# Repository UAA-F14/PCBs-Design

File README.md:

# Power Electronics PCBs

Power electronics boards from coursework — physical PCB designs, not just simulation. Each folder is a separate board with its own schematic/layout, a 3D render, and (coming soon) real photos of the built board.

| | Project | What it is |
|---|---|---|
|  | [`scr-controller/`](scr-controller/) | SCR/thyristor phase-control firing board |
|  | [`buck-converter-24-120v/`](buck-converter-24-120v/) | Buck converter, 24 V input target |
|  | [`classd-amplifier-stm32/`](classd-amplifier-stm32/) | Class D amplifier, STM32-controlled switching |
|  | [`power-supply-protected/`](power-supply-protected/) | Voltage supply with short-circuit protection (power + control boards) |
|  | [`ac-dc-inverter/`](ac-dc-inverter/) | AC-DC inverter |

All of these were built as coursework together with [Iker Garcia](https://github.com/IKGB105) [DasReyxr](https://github.com/DasReyxr) and [Kevin Lara](https://github.com/Gyonyu) — the original combined project history lives in [DasReyxr/HW-Projects](https://github.com/DasReyxr/HW-Projects). This repo pulls out just the PCB projects, one per folder, with proper writeups and renders instead of a mixed dump of exam/simulation files.

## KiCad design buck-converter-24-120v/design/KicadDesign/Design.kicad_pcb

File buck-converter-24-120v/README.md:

# Buck Converter (24 V &rarr; 120 V design exam)

A buck converter built for a power electronics exam. 

## Directory structure
```
├── design
│   ├── SCRController
│   │   ├── Design.kicad_pcb
│   │   ├── Design.kicad_pro
│   │   ├── Design.kicad_sch
│   └── Schematic.pdf
├── README.md
├── src
│   └── render.png
├── sim
    └── BuckConv.ms14
    └── simulation.asc
```

- `BuckConverter.kicad_sch` / `.kicad_pcb` / `.kicad_pro` — KiCad design
- `Schematic.pdf` — schematic printout
- `simulation.asc` — LTspice simulation

**Photos of the built board — coming soon**

## Credit
Built as coursework with [DasReyxr](https://github.com/DasReyxr)  and [Kevin Lara](https://github.com/Gyonyu) — original project history in [DasReyxr/HW-Projects](https://github.com/DasReyxr/HW-Projects). This copy is curated separately with a proper writeup and renders.

## Template
```
mkdir code design doc scripts sim src
```

```
tree >> Readme.md
```

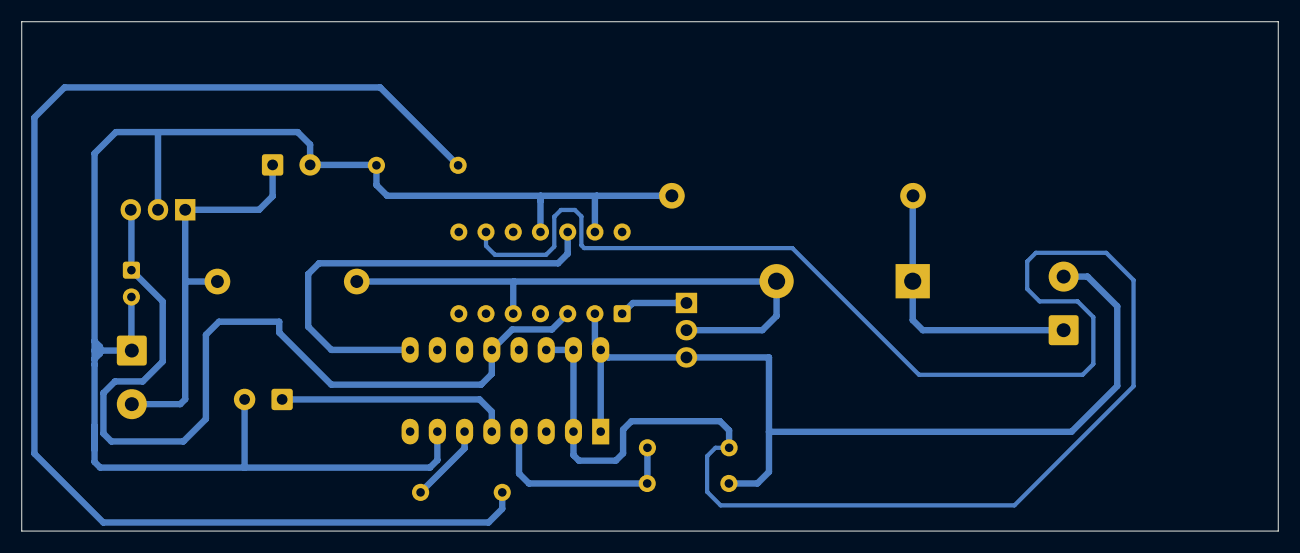
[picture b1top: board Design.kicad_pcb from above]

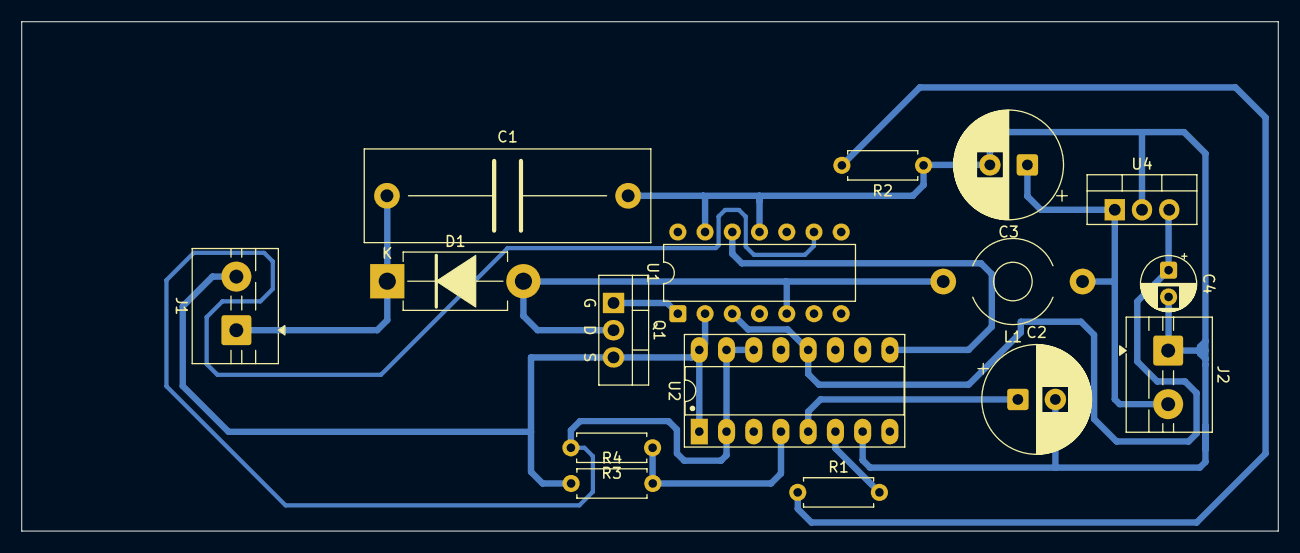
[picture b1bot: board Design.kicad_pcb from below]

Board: 2 copper layers, 117.2 x 47.5 mm, 16 parts (16 on the bottom side), 12 nets.

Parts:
C1: C_Rect_L26.5mm_W8.5mm_P22.50mm; C_Rect_L26.5mm_W8.5mm_P22.50mm_MKS4
C2: 1nF; CP_Radial_D10.0mm_P3.50mm
C3: 470n; CP_Radial_D10.0mm_P3.50mm
C4: 0.1u; CP_Radial_D5.0mm_P2.50mm
D1: MUR460; D_DO-201AD_P12.70mm_Horizontal
J1, J2: Screw_Terminal_01x02; TerminalBlock_MaiXu_MX126-5.0-02P_1x02_P5.00mm
L1: L; L_Toroid_Horizontal_D7.8mm_P13.00mm_Diameter9-5mm_Amidon-T30
Q1: IRF740; TO-220-3_Vertical_GDS
R1, R2, R3, R4: R_0201; R_Axial_DIN0207_L6.3mm_D2.5mm_P7.62mm_Horizontal
U1: IR2110; DIP-14_W7.62mm
U2: TL494; DIP-16_W7.62mm_Socket_LongPads
U4: LM7809CT; TO-220-3_Vertical

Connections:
9V: C4.1, U1.3 (VCC), U2.12 (VCC), U4.3 (OUT)
24V: C3.1, J2.2, L1.1, U4.1 (IN)
D: D1.2 (A), L1.2, Q1.2 (D), U1.5 (VS)
GND: C1.2, C2.2, C3.2, C4.2, J1.2, J2.1, Q1.3 (S), R2.1, R4.1, U1.2 (COM), U1.11 (SD), U1.13 (VSS), U2.1 (1IN+), U2.7 (GND), U2.16 (2IN+), U4.2
unnamed: C1.1, D1.1 (K), J1.1
unnamed: Q1.1 (G), U1.1 (LO)
unnamed: R1.1, R2.2
unnamed: C2.1, U2.5 (CT)
unnamed: R3.1, R4.2, U2.4 (DTC)
unnamed: R1.2, U2.6 (RT)
PWMOUT: U1.12 (LIN), U2.9 (E1)
REF: R3.2, U1.9 (VDD), U2.2 (1IN-), U2.14 (REF), U2.15 (2IN-)

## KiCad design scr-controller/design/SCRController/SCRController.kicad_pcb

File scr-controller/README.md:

# SCR (Thyristor) Firing Controller

A didactic board for triggering SCRs/thyristors — a phase-control firing circuit built for a power electronics course.

## Directory structure
```
├── design
│   ├── KicadDesign
│   │   ├── Design.kicad_pcb
│   │   ├── Design.kicad_pro
│   │   ├── Design.kicad_sch
│   └── Schematic.pdf
├── doc
│   ├── AC
│   ├── ConfigAC.tex
│   ├── Examen1.pdf
│   ├── Examen1.tex
│   └── Tarjeta didáctica de control para tiristores.pdf
├── README.md
├── src
│   └── render.png
├── sim
│   └── SCR.asc
```

- `SCRController.kicad_sch` / `.kicad_pcb` / `.kicad_pro` — KiCad design
- `SCRController.step` — 3D model
- `Tarjeta didáctica de control para tiristores.pdf` — design writeup
- `simulation.asc.txt` — LTspice simulation

**Photos of the built board — coming soon**

## Files

## Credit
Built as coursework with [DasReyxr](https://github.com/DasReyxr)  and [Kevin Lara](https://github.com/Gyonyu) — original project history in [DasReyxr/HW-Projects](https://github.com/DasReyxr/HW-Projects). This copy is curated separately with a proper writeup and renders.

## Template
```
mkdir code design doc scripts sim src
```

```
tree >> README.md
```

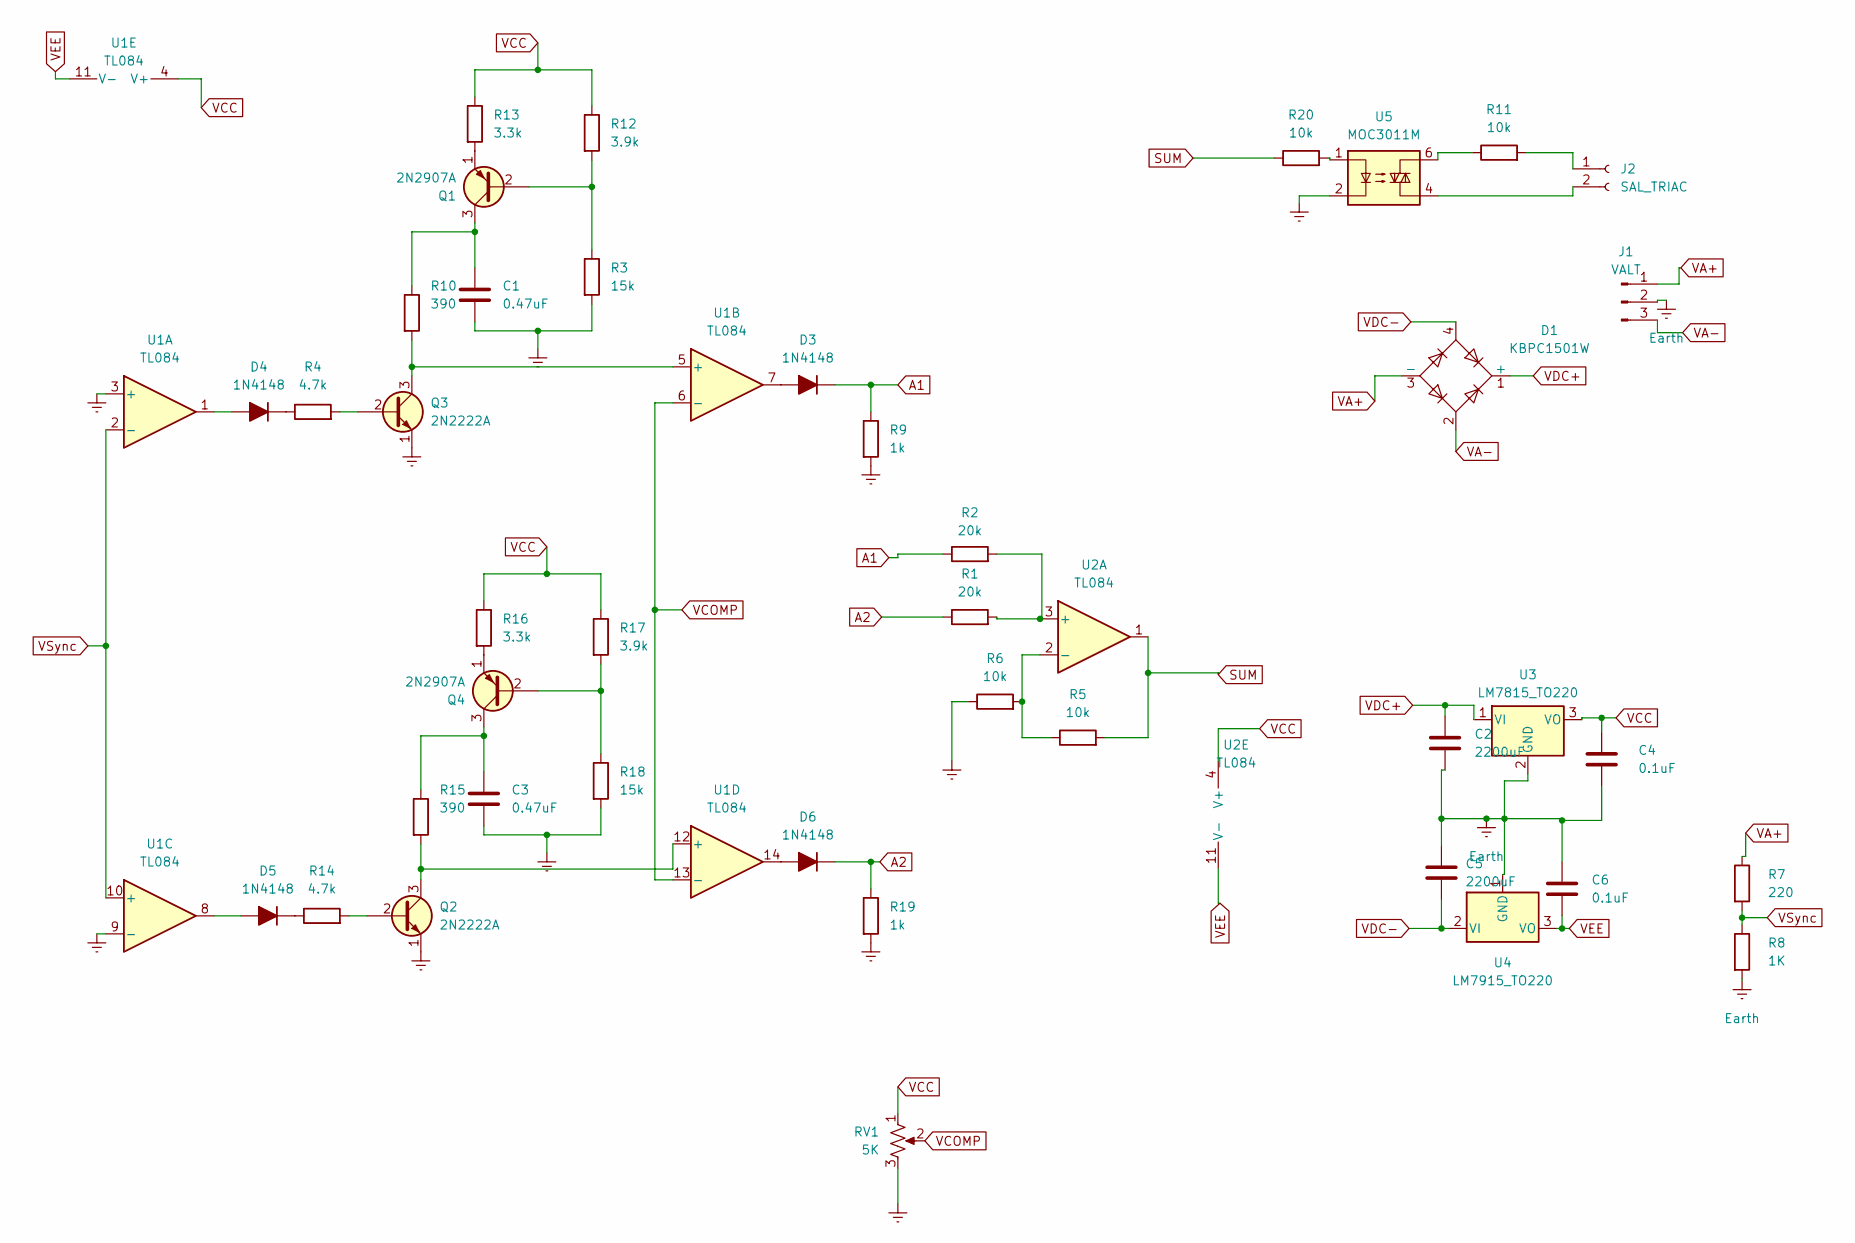
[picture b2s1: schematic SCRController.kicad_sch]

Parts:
C1, C3: 0.47uF; C_Radial_D4.0mm_H5.0mm_P1.50mm
C2, C5: 2200uF; C_Radial_D12.5mm_H25.0mm_P5.00mm
C4, C6: 0.1uF; C_Radial_D4.0mm_H5.0mm_P1.50mm
D1: KBPC1501W; Diode_Bridge_KBP
D3, D4, D5, D6: 1N4148; D_DO-15_P5.08mm_Vertical_AnodeUp
J1: VALT; TerminalBlock_MaiXu_MX126-5.0-03P_1x03_P5.00mm
J2: SAL_TRIAC; TerminalBlock_MaiXu_MX126-5.0-02P_1x02_P5.00mm
Q1, Q4: 2N2907A; TO-92L_Inline_Wide
Q2, Q3: 2N2222A; TO-92L_Inline_Wide
R1, R2: 20k; R_Axial_DIN0207_L6.3mm_D2.5mm_P7.62mm_Horizontal
R3, R18: 15k; R_Axial_DIN0207_L6.3mm_D2.5mm_P7.62mm_Horizontal
R4, R14: 4.7k; R_Axial_DIN0207_L6.3mm_D2.5mm_P7.62mm_Horizontal
R5, R6, R11, R20: 10k; R_Axial_DIN0207_L6.3mm_D2.5mm_P7.62mm_Horizontal
R7: 220; R_Axial_DIN0207_L6.3mm_D2.5mm_P7.62mm_Horizontal
R8: 1K; R_Axial_DIN0207_L6.3mm_D2.5mm_P7.62mm_Horizontal
R9, R19: 1k; R_Axial_DIN0207_L6.3mm_D2.5mm_P7.62mm_Horizontal
R10, R15: 390; R_Axial_DIN0207_L6.3mm_D2.5mm_P7.62mm_Horizontal
R12, R17: 3.9k; R_Axial_DIN0207_L6.3mm_D2.5mm_P7.62mm_Horizontal
R13, R16: 3.3k; R_Axial_DIN0207_L6.3mm_D2.5mm_P7.62mm_Horizontal
RV1: 5K; Potentiometer_Alps_RK163_Single_Horizontal
U1, U2: TL084; DIP-14_W7.62mm_LongPads
U3: LM7815_TO220; TO-220-3_Vertical
U4: LM7915_TO220; TO-220-3_Vertical
U5: MOC3011M; DIP-6_W7.62mm_LongPads

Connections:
A1: D3.1 (K), R2.1, R9.1
A2: D6.1 (K), R1.1, R19.1
Earth: C1.2, C2.2, C3.2, C4.2, C5.1, C6.1, J1.2, Q2.1 (E), Q3.1 (E), R3.2, R6.1, R8.2, R9.2, R18.2, R19.2, RV1.3, U1.3 (+), U1.9 (-), U3.2 (GND), U4.1 (GND), U5.2
unnamed: D3.2 (A), U1.7
unnamed: D4.2 (A), U1.1
unnamed: D4.1 (K), R4.1
unnamed: D5.2 (A), U1.8
unnamed: D5.1 (K), R14.1
unnamed: D6.2 (A), U1.14
unnamed: J2.1, R11.2
unnamed: J2.2, U5.4
unnamed: Q1.2 (B), R3.1, R12.2
unnamed: C1.1, Q1.3 (C), R10.1
unnamed: Q1.1 (E), R13.2
unnamed: Q2.2 (B), R14.2
unnamed: Q2.3 (C), R15.2, U1.12 (+)
unnamed: Q3.2 (B), R4.2
unnamed: Q3.3 (C), R10.2, U1.5 (+)
unnamed: Q4.2 (B), R17.2, R18.1
unnamed: C3.1, Q4.3 (C), R15.1
unnamed: Q4.1 (E), R16.2
unnamed: R11.1, U5.6
unnamed: R20.2, U5.1
unnamed: R1.2, R2.2, U2.3 (+)
unnamed: R5.1, R6.2, U2.2 (-)
SUM: R5.2, R20.1, U2.1
VA+: D1.3 (-), J1.1, R7.1
VA-: D1.2, J1.3
VCC: C4.1, R12.1, R13.1, R16.1, R17.1, RV1.1, U1.4 (V+), U2.4 (V+), U3.3 (VO)
VCOMP: RV1.2, U1.6 (-), U1.13 (-)
VDC+: C2.1, D1.1 (+), U3.1 (VI)
VDC-: C5.2, D1.4, U4.2 (VI)
VEE: C6.2, U1.11 (V-), U2.11 (V-), U4.3 (VO)
VSync: R7.2, R8.1, U1.2 (-), U1.10 (+)

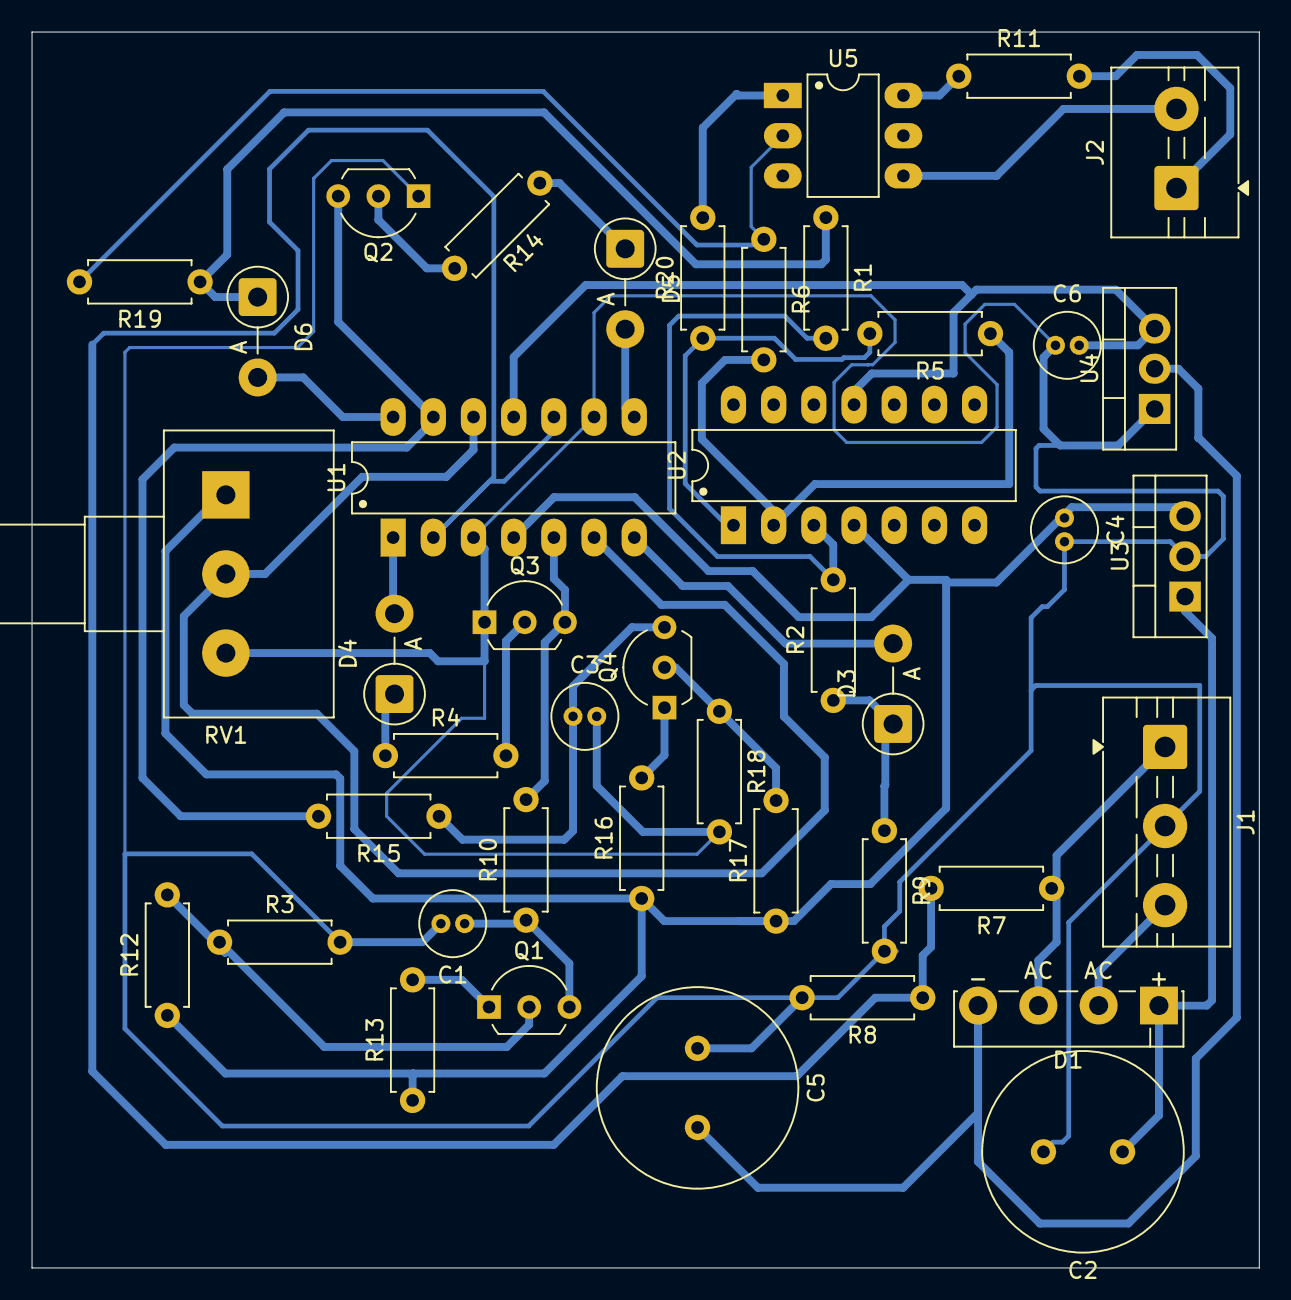
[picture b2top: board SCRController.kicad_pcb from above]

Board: 2 copper layers, 77.6 x 78.1 mm, 43 parts (0 on the bottom side), 34 nets.

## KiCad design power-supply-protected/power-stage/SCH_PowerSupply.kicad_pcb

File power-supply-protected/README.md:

# Protected Voltage Supply (Two-Board System)

A voltage supply with short-circuit protection, split across two boards: a **power stage** (the actual supply, fully routed with fabrication-ready Gerbers) and a **control stage** (protection/sensing logic built around a CD4043BE tri-state buffer).

## Directory structure
```
├── design
│   ├── SCH_PowerSupply
│   └── SCH_PowerSupply.pdf
├── doc
│   ├── generalconfig.tex
│   ├── PowerSupply.pdf
│   ├── PowerSupply.tex
│   ├── sn-jnl.cls
├── Power_Supply.pdf
├── README.md
├── sim
│   └── PowerSupply.ms14
└── src
    └── render.png
```

- `power-stage/` — `SCH_PowerSupply.kicad_*`, full Gerbers + drill files in `gerbers/`, PDF writeup
- `control-stage/` — `CONTROL_PowerSupply.kicad_*`, CD4043BE symbol
- `Power_Supply.pdf` — overall design writeup
- 

**Photos of the built boards — coming soon**

## Credit
Built as coursework with [DasReyxr](https://github.com/DasReyxr) and [Kevin Lara](https://github.com/Gyonyu) — original project history in [DasReyxr/HW-Projects](https://github.com/DasReyxr/HW-Projects). This copy is curated separately with a proper writeup and renders.

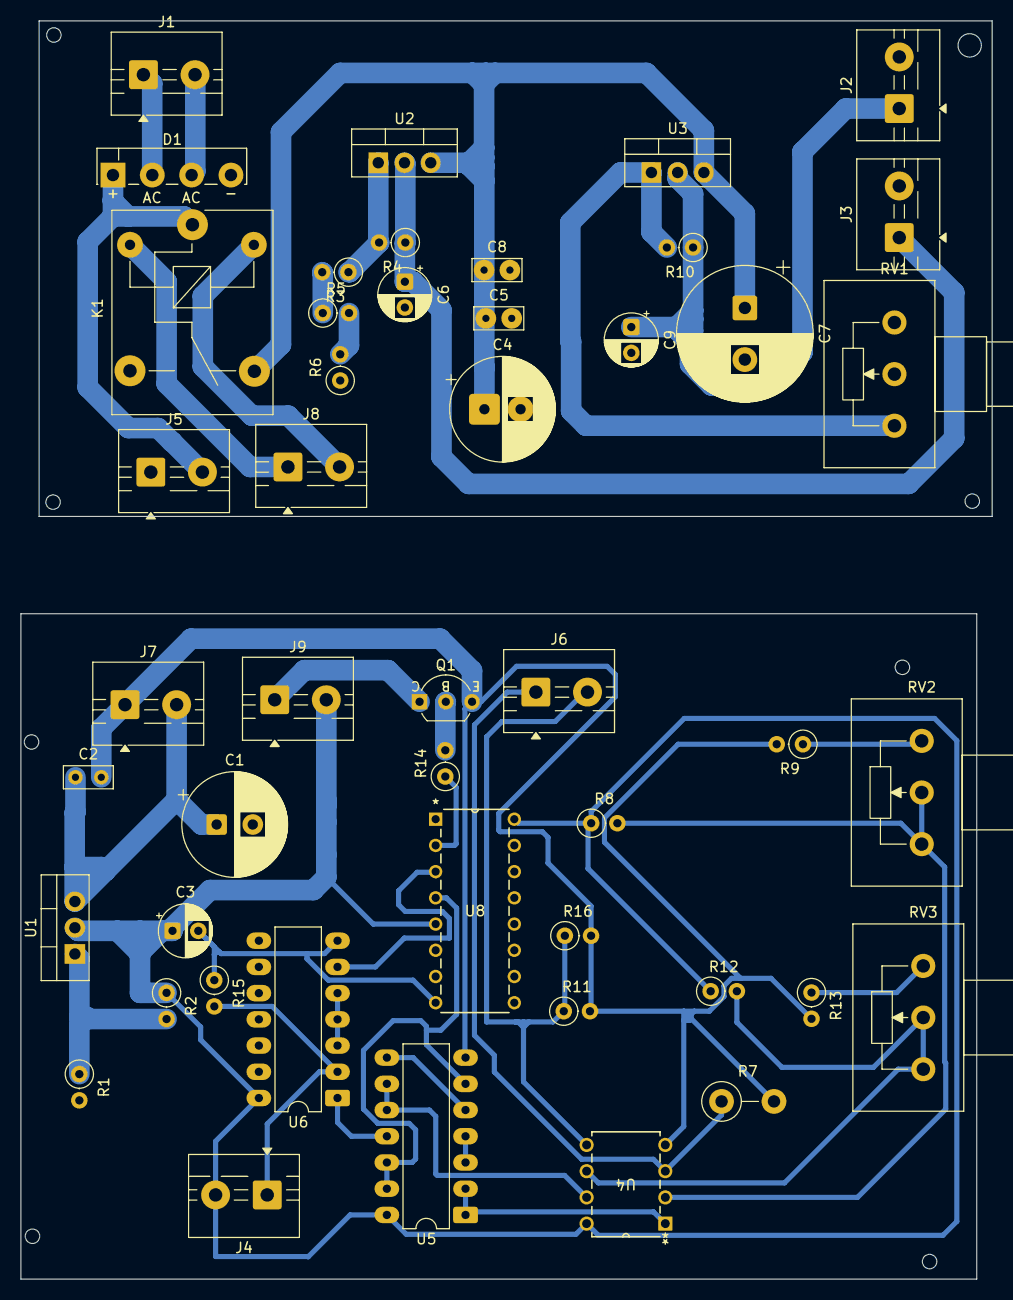
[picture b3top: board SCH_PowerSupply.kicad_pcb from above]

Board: 2 copper layers, 94.1 x 121.9 mm, 47 parts (0 on the bottom side), 35 nets.

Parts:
C1, C4: 220u; CP_Radial_D10.0mm_P3.50mm
C2, C5, C8: 0.1u; C_Rect_L4.6mm_W2.0mm_P2.50mm_MKS02_FKP02
C3, C6, C9: 1u; CP_Radial_D5.0mm_P2.50mm
C7: 680u; CP_Radial_D13.0mm_P5.00mm
D1: KBP206G; Diode_Bridge_KBP
J1, J2, J3, J4, J5, J6, J7, J8, J9: Screw_Terminal_01x02; TerminalBlock_MaiXu_MX126-5.0-02P_1x02_P5.00mm
K1: SANYOU_SRD_Form_C; Relay_SPDT_SANYOU_SRD_Series_Form_C
Q1: BC547B; TO-92_Inline_Wide_CBE
R1, R16: 1k; R_Axial_DIN0207_L6.3mm_D2.5mm_P2.54mm_Vertical
R2, R3: 330; R_Axial_DIN0207_L6.3mm_D2.5mm_P2.54mm_Vertical
R4, R9, R13, R15: 220; R_Axial_DIN0207_L6.3mm_D2.5mm_P2.54mm_Vertical
R5: 22; R_Axial_DIN0207_L6.3mm_D2.5mm_P2.54mm_Vertical
R6: 10; R_Axial_DIN0207_L6.3mm_D2.5mm_P2.54mm_Vertical
R7: 0.15; R_Axial_DIN0411_L9.9mm_D3.6mm_P5.08mm_Vertical
R8, R12: 10k; R_Axial_DIN0207_L6.3mm_D2.5mm_P2.54mm_Vertical
R10: 470; R_Axial_DIN0207_L6.3mm_D2.5mm_P2.54mm_Vertical
R11: 0.15; R_Axial_DIN0207_L6.3mm_D2.5mm_P2.54mm_Vertical
R14: 15k; R_Axial_DIN0207_L6.3mm_D2.5mm_P2.54mm_Vertical
RV1: 5k; Potentiometer_Alps_RK163_Single_Horizontal
RV2, RV3: 10k; Potentiometer_Alps_RK163_Single_Horizontal
U1, U2, U3: LM317T; TO-220-3_Vertical
U4: LM358P
U5, U6: 74LS00; DIP-14_W7.62mm_LongPads
U8: CD4043BE; PIN16

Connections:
3.3GIN: J6.1, R7.1, U4.3 (+)
5V: C3.1, J4.2, J9.2, R2.1, R8.1, R12.1, U1.2 (OUT), U4.8 (V+), U5.14 (VCC), U6.14 (VCC), U8.5 (EN), U8.16 (VDD)
5V_C: J8.2, K1.5
15GIN: J6.2, R11.1, R16.1, U4.5 (+)
BJT: R14.1, U8.2 (Q1)
GND: C4.2, C5.2, C6.2, C7.2, C8.2, C9.2, D1.4 (-), J5.1, R6.1, RV1.2, RV1.3
GND_C: C1.2, C2.2, C3.2, J7.1, Q1.3 (E), R1.2, R7.2, R9.2, R11.2, R13.2, R15.1, R16.2, U4.4 (V-), U5.7 (GND), U6.7 (GND), U8.8 (VSS)
unnamed: D1.2 (1), J1.1
unnamed: D1.3 (2), J1.2
unnamed: C9.1, J2.1, R10.1, U3.2 (OUT)
unnamed: C6.1, J3.1, R4.1, U2.2 (OUT)
unnamed: Q1.2 (B), R14.2
unnamed: R1.1, R2.2, U1.1
unnamed: R3.1, R4.2, U2.1
unnamed: R3.2, R5.1
unnamed: R5.2, R6.2
unnamed: R9.1, RV2.3
unnamed: R10.2, RV1.1, U3.1
unnamed: R13.1, RV3.3
unnamed: R8.2, RV2.1, RV2.2, U4.2 (-)
unnamed: R12.2, RV3.1, RV3.2, U4.6 (-)
unnamed: U5.3, U5.4
unnamed: U5.5, U5.8
unnamed: U5.11, U6.1
unnamed: U6.3, U6.4, U6.5
REG5: D1.1 (+), J5.2, K1.1
RELE: J9.1, Q1.1 (C)
RELE_C: J8.1, K1.2
RST: U6.6, U8.3 (R1)
SC: U5.6, U5.12, U5.13, U8.4 (S1)
SC3.3: U4.1, U5.1, U5.2
SC15: U4.7, U5.9, U5.10
SW: J4.1, R15.2, U6.2
VAC: C4.1, C5.1, C7.1, C8.1, K1.4, U2.3 (IN), U3.3 (IN)
V_C: C1.1, C2.1, J7.2, U1.3 (IN)
